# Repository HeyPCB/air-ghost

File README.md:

# Air Ghost

**A little ghost that blushes red when your room needs fresh air.**

Air Ghost is a desk CO2 monitor shaped like a ghost, on USB-C. A Sensirion SCD40 measures real CO2 (photoacoustic NDIR, not a VOC estimate) plus temperature and humidity every 5 s, and a CH32V003 turns the reading into the colour of the ghost's two WS2812 cheeks: green when the air is fresh, through yellow and orange to a pulsing red at 2000 ppm. Its round "O" mouth is a button: boop it for temperature and humidity colours, hold it for night mode.

| Layers | Size | Parts | Nets | Connections routed | Vias | ERC errors | DRC errors / unconnected / parity | BOM @100 |
|---|---|---|---|---|---|---|---|---|
| 2 | 50.7 x 62.3 mm | 16 (+3 pads) | 12 | 50 -> 0 open | 10 | 0 | 0 / 0 / 0 | $15.66 |

**Not fabricated, assembled or powered yet.** Every number on this page is measured by KiCad 10.0.6 on
the files in this repository ([`report.json`](report.json), [`measured.json`](measured.json)) or read
from the live JLC/LCSC catalogue ([`bom_cost.json`](bom_cost.json)).

| | |
|---|---|
| Spec, power budget, BOM | [`SPEC.md`](SPEC.md) |
| Store copy | [`STORE_COPY.md`](STORE_COPY.md) |
| KiCad 10 project | [`kicad/`](kicad/) |
| Gerbers, drill, BOM, CPL, STEP, schematic PDF | [`fab/`](fab/) |
| Firmware | [`firmware/`](firmware/) |
| Renders | [front](media/top.png), [back](media/bottom.png), [hero](media/hero.png), [Circuit World thumbnail](media/circuit-world.png) |
| Brief and generator | [`design/`](design/) |

## What's on it

- **Sensor:** Sensirion SCD40-D-R2 (CO2 400-2000 ppm, temperature, humidity) at I2C 0x62, from 5 V, with 10 uF + 100 nF beside it and 10k pull-ups.
- **MCU:** CH32V003F4P6 from 5 V; bit-banged I2C with CRC checks (ch32fun's static_i2c.h).
- **Cheeks:** two WS2812C-2020 RGB LEDs, each with its 100 nF, chained from PC6.
- **Mouth:** a TS-1187A button; its round plunger is the ghost's "O".
- **Power:** USB-C with 5.1 kOhm CC pull-downs, about 25 mA (SPEC.md).
- **BOM:** $15.66 at 100, of which the SCD40 is $14.82: the collection's one deliberate exception to its $8 target (SPEC.md says why).

## Finish

White solder mask, Black silkscreen, ENIG copper finish, 1.6 mm FR4, top-side SMT assembly (J1: an SMD part whose shell legs go through plated holes, soldered on the same SMT line).
The gold art is bare copper under a mask opening (ENIG), drawn with its own keep-out so no track runs
under it. The QR code on the back opens [https://heypcb.ai/world/b/0fc87b5d15f5](https://heypcb.ai/world/b/0fc87b5d15f5).

## How it was made

Designed with the HeyPCB method on KiCad 10.0.6, headless, by the `heypcb-kicad` pipeline: a written
brief composed from reusable circuit blocks, every pin from KiCad's own symbol library, every part bound
to an LCSC number from a dated catalogue read, then ERC, a netlist round trip, locked placement,
Freerouting 2.4.1, pours, silkscreen and board art, DRC with schematic parity, DFM and a fab gate,
each stage gated by a measurement. `design/make_brief.py` regenerates the brief (outline, part
locks and art) from code.

Part of the [heypcb.ai merch collection](https://github.com/HeyPCB/merch).

## License

Hardware: [CERN-OHL-S v2](LICENSE). Firmware: MIT (see [`firmware/LICENSE`](firmware/LICENSE)). KiCad's symbol, footprint and 3D
libraries used in the design are CC-BY-SA 4.0 with the KiCad library exception.

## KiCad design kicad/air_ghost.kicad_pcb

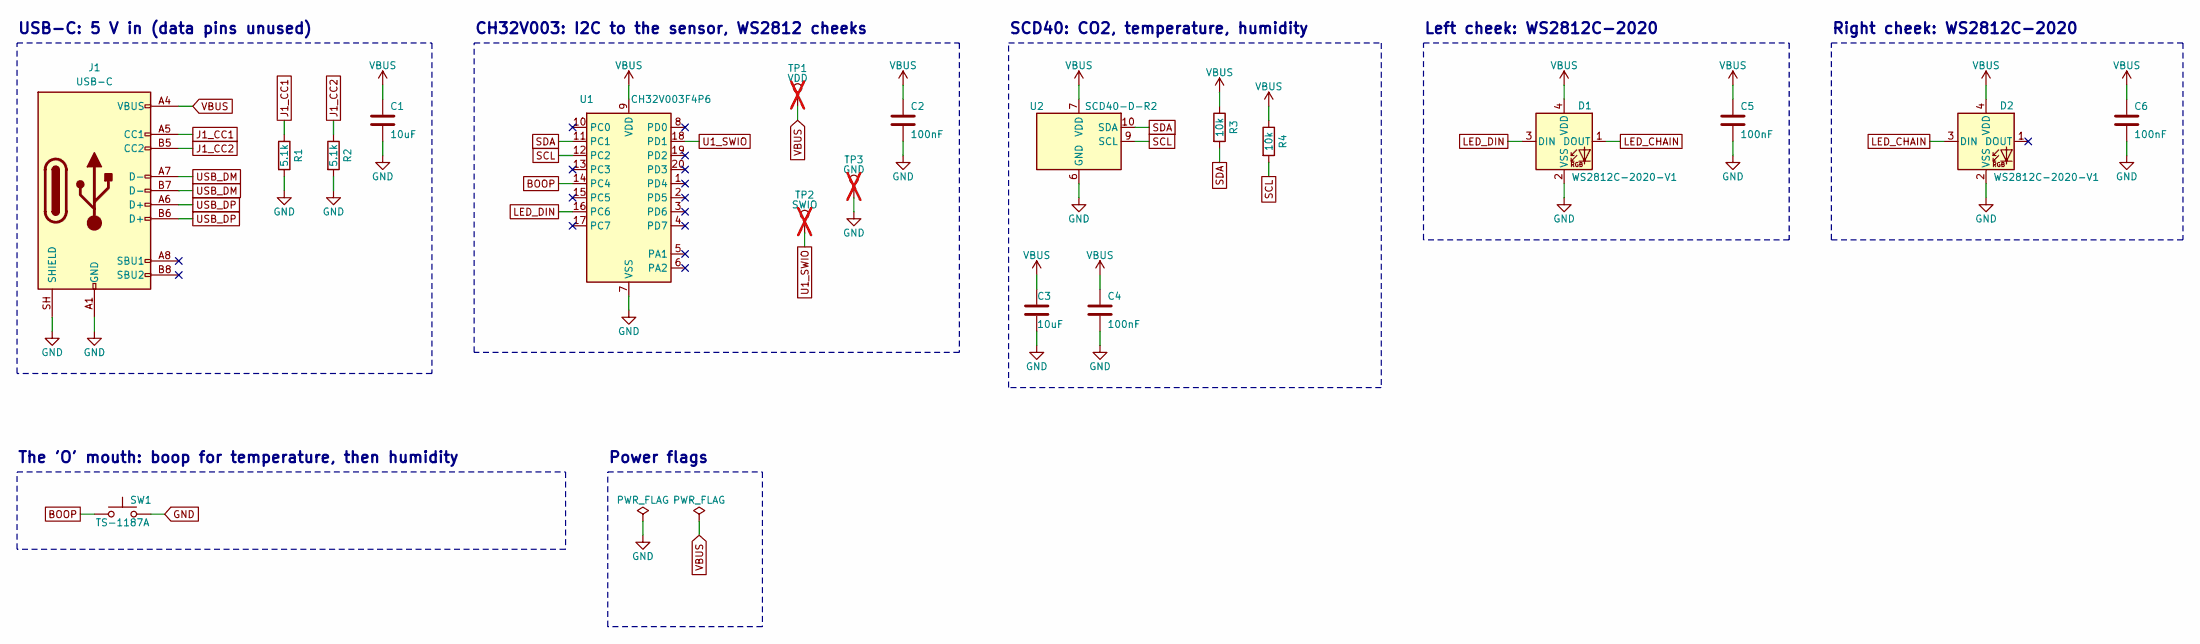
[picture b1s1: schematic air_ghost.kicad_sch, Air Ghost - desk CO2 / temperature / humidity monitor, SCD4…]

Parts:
C1, C3: 10uF; C_0805_2012Metric; MPN CL21A106KAYNNNE; LCSC C15850
C2, C4: 100nF; C_0603_1608Metric; MPN CC0603KRX7R9BB104; LCSC C14663
C5, C6: 100nF; C_0402_1005Metric; MPN CL05B104KO5NNNC; LCSC C1525
D1, D2: WS2812C-2020-V1; LED_WS2812B-2020_PLCC4_2.0x2.0mm; MPN WS2812C-2020-V1; LCSC C2976072
J1: USB-C; USB_C_Receptacle_HRO_TYPE-C-31-M-12; MPN TYPE-C-31-M-12; LCSC C165948
R1, R2: 5.1k; R_0402_1005Metric; MPN 0402WGF5101TCE; LCSC C25905
R3, R4: 10k; R_0402_1005Metric; MPN 0402WGF1002TCE; LCSC C25744
SW1: TS-1187A; SW_Push_1P1T_XKB_TS-1187A; MPN TS-1187A-B-A-B; LCSC C318884
TP1: VDD; TestPoint_Pad_1.0x1.0mm; not fitted
TP2: SWIO; TestPoint_Pad_1.0x1.0mm; not fitted
TP3: GND; TestPoint_Pad_1.0x1.0mm; not fitted
U1: CH32V003F4P6; TSSOP-20_4.4x6.5mm_P0.65mm; MPN CH32V003F4P6; LCSC C5187096
U2: SCD40-D-R2; Sensirion_SCD4x-1EP_10.1x10.1mm_P1.25mm_EP4.8x4.8mm; MPN SCD40-D-R2; LCSC C3659421

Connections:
BOOP: SW1.1, U1.14 (PC4)
GND: C1.2, C2.2, C3.2, C4.2, C5.2, C6.2, D1.2 (VSS), D2.2 (VSS), J1.A1 (GND), J1.A12 (GND), J1.B1 (GND), J1.B12 (GND), J1.SH (SHIELD), R1.2, R2.2, SW1.2, TP3.1, U1.7 (VSS), U2.6 (GND), U2.20 (GND), U2.21 (GND)
J1_CC1: J1.A5 (CC1), R1.1
J1_CC2: J1.B5 (CC2), R2.1
LED_CHAIN: D1.1 (DOUT), D2.3 (DIN)
LED_DIN: D1.3 (DIN), U1.16 (PC6)
SCL: R4.2, U1.12 (PC2), U2.9 (SCL)
SDA: R3.2, U1.11 (PC1), U2.10 (SDA)
U1_SWIO: TP2.1, U1.18 (PD1)
USB_DM: J1.A7 (D-), J1.B7 (D-)
USB_DP: J1.A6 (D+), J1.B6 (D+)
VBUS: C1.1, C2.1, C3.1, C4.1, C5.1, C6.1, D1.4 (VDD), D2.4 (VDD), J1.A4 (VBUS), J1.A9 (VBUS), J1.B4 (VBUS), J1.B9 (VBUS), R3.1, R4.1, TP1.1, U1.9 (VDD), U2.7 (VDD), U2.19 (VDD)

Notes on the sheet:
USB-C: 5 V in (data pins unused)
CH32V003: I2C to the sensor, WS2812 cheeks
SCD40: CO2, temperature, humidity
Left cheek: WS2812C-2020
Right cheek: WS2812C-2020
The 'O' mouth: boop for temperature, then humidity
Power flags

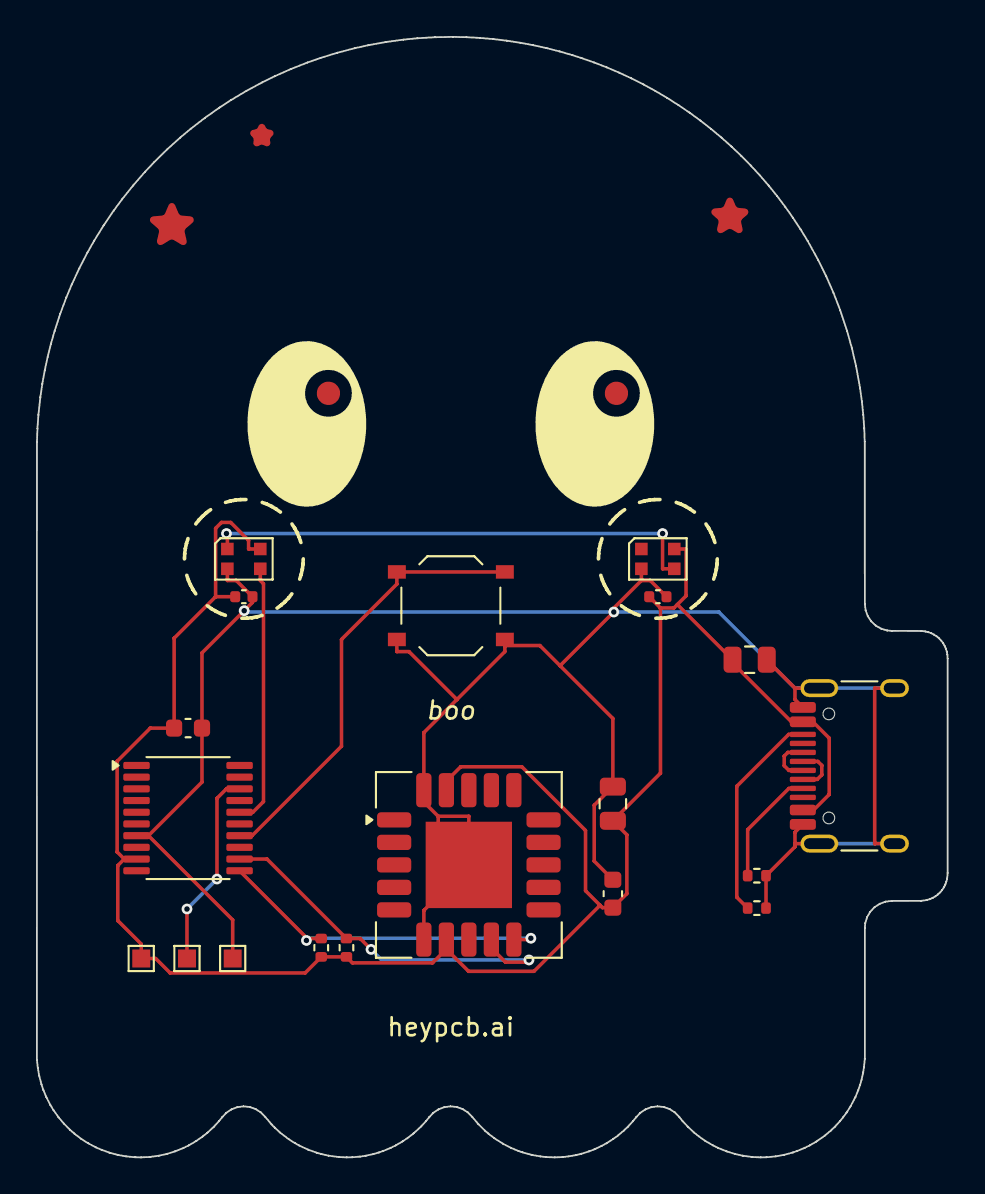
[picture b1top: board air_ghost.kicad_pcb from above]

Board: 2 copper layers, 50.6 x 62.2 mm, 19 parts (0 on the bottom side), 12 nets.

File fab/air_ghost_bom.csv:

"Reference","Value","Footprint","MPN","LCSC","Qty"
"C1,C3","10uF","Capacitor_SMD:C_0805_2012Metric","CL21A106KAYNNNE","C15850","2"
"C2,C4","100nF","Capacitor_SMD:C_0603_1608Metric","CC0603KRX7R9BB104","C14663","2"
"C5,C6","100nF","Capacitor_SMD:C_0402_1005Metric","CL05B104KO5NNNC","C1525","2"
"D1,D2","WS2812C-2020-V1","LED_SMD:LED_WS2812B-2020_PLCC4_2.0x2.0mm","WS2812C-2020-V1","C2976072","2"
"J1","USB-C","Connector_USB:USB_C_Receptacle_HRO_TYPE-C-31-M-12","TYPE-C-31-M-12","C165948","1"
"R1,R2","5.1k","Resistor_SMD:R_0402_1005Metric","0402WGF5101TCE","C25905","2"
"R3,R4","10k","Resistor_SMD:R_0402_1005Metric","0402WGF1002TCE","C25744","2"
"SW1","TS-1187A","Button_Switch_SMD:SW_Push_1P1T_XKB_TS-1187A","TS-1187A-B-A-B","C318884","1"
"U1","CH32V003F4P6","Package_SO:TSSOP-20_4.4x6.5mm_P0.65mm","CH32V003F4P6","C5187096","1"
"U2","SCD40-D-R2","Sensor:Sensirion_SCD4x-1EP_10.1x10.1mm_P1.25mm_EP4.8x4.8mm","SCD40-D-R2","C3659421","1"

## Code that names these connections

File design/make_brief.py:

"""Writes boards/merch_air_ghost/board.json: Air Ghost, the desk CO2 monitor (heypcb.ai merch 05).

    "$KICAD_PYTHON" boards/merch_air_ghost/make_brief.py

A little white ghost that blushes green when the air is fresh and red when the room needs a window
opened. A Sensirion SCD40 measures real CO2 (photoacoustic NDIR, not a VOC estimate) plus temperature
and humidity; a CH32V003 from USB-C turns it into the colour of two WS2812 cheeks. Its "O" mouth is
the button. Edit this file, not board.json. Frame 58 x 68 mm, origin top-left, y down.
"""
import os
import sys

HERE = os.path.dirname(os.path.abspath(__file__))
sys.path.insert(0, os.path.dirname(HERE))
import merch_kit as K  # noqa: E402

SLUG = "air-ghost"
W, H = 58.0, 68.0
CX = 28.0
EYE_Y = 23.5

MCU_PINS = {"U?.11": "SDA", "U?.12": "SCL", "U?.16": "LED_DIN", "U?.14": "BOOP"}
MCU_NC = ["U?.%d" % p for p in (1, 2, 3, 4, 5, 6, 8, 10, 13, 15, 17, 19, 20)]

BLOCKS = [
    {"block": "usb_c_data_5v", "as": "usb", "title": "USB-C: 5 V in (data pins unused)",
     "nets": {"USB_DP": "USB_DP", "USB_DM": "USB_DM"}},
    {"block": "merch_mcu_ch32v003", "as": "mcu", "title": "CH32V003: I2C to the sensor, WS2812 cheeks",
     "nets": {"VDD": "VBUS"}, "pinNets": MCU_PINS, "no_connect": MCU_NC},
    {"block": "merch_scd40", "as": "co2", "title": "SCD40: CO2, temperature, humidity",
     "nets": {"VDD": "VBUS", "SDA": "SDA", "SCL": "SCL"}},
    {"block": "irisring_pixel", "as": "cheek_l", "title": "Left cheek: WS2812C-2020",
     "nets": {"VDD": "VBUS"}, "pinNets": {"D?.3": "LED_DIN", "D?.1": "LED_CHAIN"}},
    {"block": "irisring_pixel", "as": "cheek_r", "title": "Right cheek: WS2812C-2020",
     "nets": {"VDD": "VBUS"}, "pinNets": {"D?.3": "LED_CHAIN"}, "no_connect": ["D?.1"]},
    {"block": "merch_button", "as": "mouth", "title": "The 'O' mouth: boop for temperature, then humidity",
     "nets": {"SIG": "BOOP"}},
]

# ---------------------------------------------------------------------------------------- outline
dome = K.Shape.circle(CX, 25.0, 23.0)
body = K.Shape.rect(5.0, 25.0, 51.0, 59.0)
hem = K.Shape.rect(0, 0, 0.1, 0.1)
for x in (10.75, 22.25, 33.75, 45.25):
    hem = hem | K.Shape.circle(x, 58.5, 5.75)
usb_flat = K.Shape.rect(44.0, 35.0, 55.6, 50.0)
outline = (dome | body | hem | usb_flat).rounded(1.5)

# ---------------------------------------------------------------------------------------- parts
parts = K.design_footprints(BLOCKS, os.path.join(os.path.dirname(HERE), "..", "blocks"))
L = K.Layout(parts)
L.lock("mouth:SW?", CX, 33.6, 0, "the 'O' mouth")
L.lock("cheek_l:D?", CX - 11.5, 31.0, 0, "left blush")
L.lock("cheek_r:D?", CX + 11.5, 31.0, 0, "right blush")
L.lock("cheek_l:C?", CX - 11.5, 33.1, 0, "inside the blush ring")
L.lock("cheek_r:C?", CX + 11.5, 33.1, 0, "inside the blush ring")
L.lock("co2:U?", CX + 1.0, 48.0, 0, "the sensor in the belly, in open air")
L.lock("co2:C1?", CX + 9.0, 44.6, 90, "sensor bulk")
L.lock("co2:C2?", CX + 9.0, 49.6, 90, "sensor bypass")
L.lock("co2:R1?", CX - 7.2, 52.6, 90, "SDA pull-up")
L.lock("co2:R2?", CX - 5.8, 52.6, 90, "SCL pull-up")
L.lock("mcu:U?", 13.4, 45.4, 0, "MCU at the left of the belly, I2C pins toward the sensor")
L.lock("mcu:C?", 13.4, 40.4, 0, "bypass")
for i in range(3):
    L.lock("mcu:TP%d?" % (i + 1), 10.8 + 2.54 * i, 53.2, 0, "SWIO pads (VDD, SWIO, GND)")
L.lock("usb:J?", 51.6, 42.5, 90, "USB-C on the right flat, mouth out", overhang=True)
L.lock("usb:C?", 44.6, 36.6, 0, "VBUS bulk")
L.lock("usb:R1?", 45.0, 48.6, 0, "CC1 5.1k")
L.lock("usb:R2?", 45.0, 50.4, 0, "CC2 5.1k")

# ---------------------------------------------------------------------------------------- art
art = []
for sx in (-1, 1):
    ex = CX + sx * 8.0
    eye = K.Shape.ellipse(ex, EYE_Y, 3.3, 4.6)
    sparkle = K.Shape.circle(ex + 1.2, EYE_Y - 1.7, 0.95)
    art += K.silk_fill(eye - sparkle.offset(0.35), "eye")
    art += K.gold(sparkle.offset(-0.3), "eye_sparkle")
    # dashed blush round each cheek LED
    for k in range(10):
        a0 = 36.0 * k
        art += K.silk_line(K.arc_points(CX + sx * 11.5, 31.0, 3.3, a0, a0 + 20.0, 4), "blush", 0.2)
# gold stars floating by the dome
for (sx, sy, r) in ((12.5, 12.5, 1.6), (43.5, 12.0, 1.4), (17.5, 7.5, 1.0)):
    art += K.gold(K.star(sx, sy, r), "star")
art += K.text("boo", CX, 39.4, size=1.0, italic=True, name="boo")
art += K.text("heypcb.ai", CX, 57.0, size=1.0, name="brand_front")
# back: QR, the legend, the brand
art += K.qr(K.world_url(SLUG), CX, 42.0, size=12.0, side="B")
legend = ["my cheeks are the CO2:", "green < 800 ppm  yellow < 1200",
          "orange < 2000  red: open a window", "boop my mouth: temperature,",
          "boop again: humidity", "hold 2 s: night mode"]
for i, line in enumerate(legend):
    art += K.text(line, CX, 11.5 + 2.0 * i, size=1.0, side="B", name="legend%d" % i)
art += K.text("heypcb.ai", CX, 56.5, size=1.3, side="B", bold=True, name="brand_back")

keep = {}
for i, it in enumerate(a for a in art if "F.Cu" in a.get("layers", [])):
    keep["gold%d" % i] = K.Shape.poly(it["points"]).offset(0.3)
L.check(outline, edge=0.5, keep=keep)

brief = {
    "name": "air_ghost",
    "title": "Air Ghost - desk CO2 / temperature / humidity monitor, SCD40, USB-C",
    "revision": "A",
    "brief": "A ghost-shaped desk air monitor on USB-C. A Sensirion SCD40 (photoacoustic CO2 400-2000 ppm plus "
             "temperature and humidity, I2C, 5 V) is read every 5 s by a CH32V003 running from VBUS, which sets the "
             "colour of two WS2812C-2020 cheeks: green under 800 ppm through yellow and orange to red above 2000. "
             "The tactile button is the ghost's 'O' mouth: boop for temperature and humidity colours, hold for "
             "night mode. 2 layers, single-sided SMT, white mask, black silk, ENIG.",
    "blocks": BLOCKS,
    "pwrFlags": ["GND", "VBUS"],
    "netClasses": [],
    "board": {
        "width": W, "height": H, "corner_radius": 0.0, "layers": 2, "origin": [100.0, 100.0],
        "shape": {"type": "polygon", "points": K.outline_points(outline), "fillet": 0},
        "rules": {"clearance": 0.2, "track": 0.2, "via": [0.6, 0.3], "edge_clearance": 0.5,
                  "hole_to_hole": 0.5, "min_through_hole": 0.3, "min_track": 0.15},
        "finish": {"mask": "White", "silk": "Black", "copper": "ENIG",
                   "why": "a white ghost drawn in black ink; gold stars and eye sparkles"},
        "unpoured": ["F.Cu"],
        "notes": "2 layers; the face is unpoured, GND plane on the back.",
    },
    "placement": L.locks,
    "route": {"passes": 30, "fanout": True, "solve_s": 240},
    "stitch_pitch": 6.0,
    "silk": {"designators": "hide",
             "title": [{"text": "Air Ghost", "y": 26.0, "size": 1.8, "bold": True},
                       {"text": "CO2 monitor  rev {revision}", "y": 28.8, "size": 0.9}]},
    "art": art,
    "captions": {"done_3d": "Air Ghost: an SCD40 CO2 sensor in its belly, WS2812 cheeks that blush with the air."},
}
K.write_brief(os.path.join(HERE, "board.json"), brief)
print("wrote board.json: %d outline points, %d art items, %d locks, QR -> %s"
      % (len(brief["board"]["shape"]["points"]), len(art), len(L.locks), K.world_url(SLUG)))
